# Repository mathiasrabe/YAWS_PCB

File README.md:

# PCB for IOT weather station

This is the PCB of my small IOT weather station. The weatherstation consists of the following parts:

- ATtiny85 and LT1763-3.3 for power control
- TP4056 to charge the li-ion battery with solar
- BME280 to measure temperature, humidity and pressure
- ESP8266 to connect to WiFi and send the reedings via MQTT

## pictures

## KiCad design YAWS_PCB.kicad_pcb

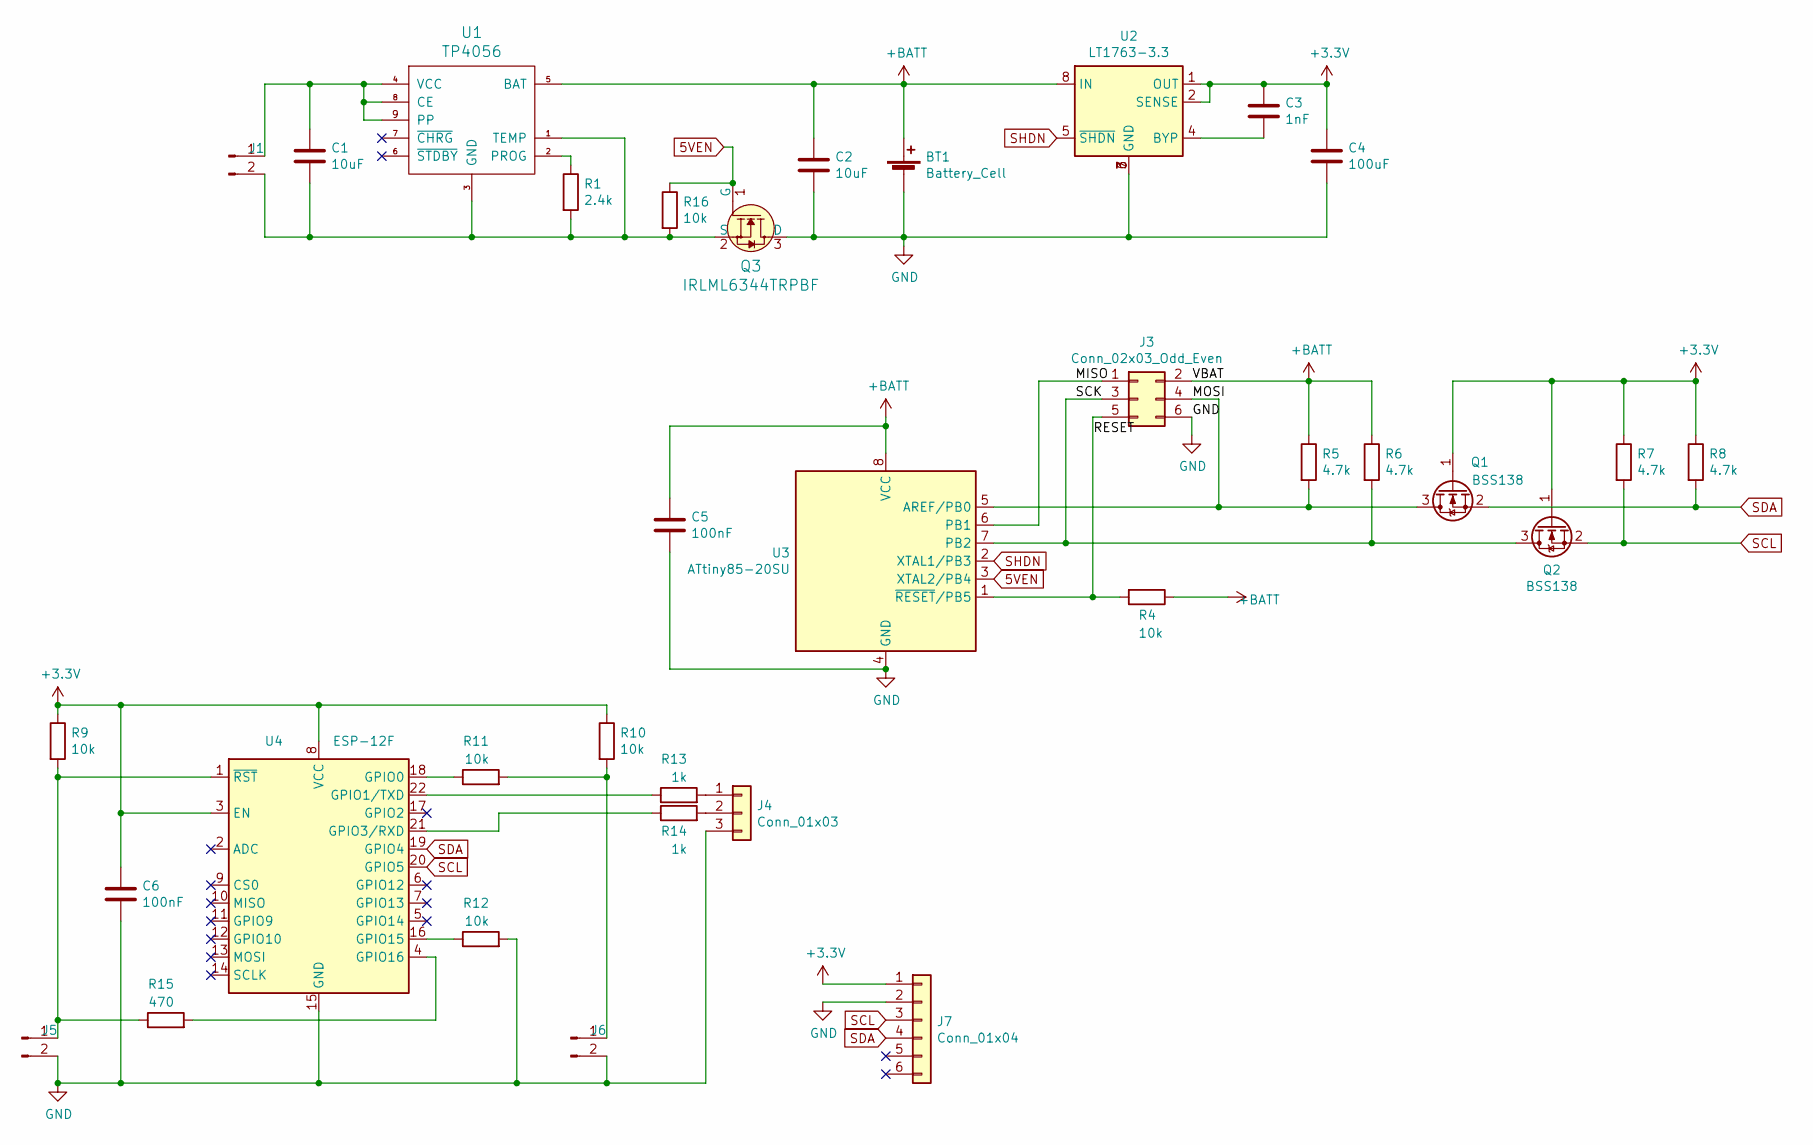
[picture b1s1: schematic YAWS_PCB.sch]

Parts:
BT1: Battery_Cell; BatteryHolder_Keystone_1042_1x18650
C1, C2: 10uF; C_0805_2012Metric
C3: 1nF; C_0805_2012Metric
C4: 100uF; CP_EIA-3528-21_Kemet-B_Pad1.50x2.35mm_HandSolder
C5, C6: 100nF; C_0805_2012Metric
J1, J5, J6: Conn_01x02_Male; PinHeader_2x01_P2.54mm_Vertical
J3: Conn_02x03_Odd_Even; PinHeader_2x03_P2.54mm_Vertical
J4: Conn_01x03; PinHeader_1x03_P2.54mm_Vertical
J7: Conn_01x04; PinSocket_1x06_P2.54mm_Vertical
Q1, Q2: BSS138; SOT-23
Q3: IRLML6344TRPBF; SOT-23-3; MPN IRLML6344TRPBF; Digi-Key_PN IRLML6344TRPBFCT-ND
R1: 2.4k; R_0805_2012Metric
R4, R9, R10, R11, R12, R16: 10k; R_0805_2012Metric
R5, R6, R7, R8: 4.7k; R_0805_2012Metric
R13, R14: 1k; R_0805_2012Metric
R15: 470; R_0805_2012Metric
U1: TP4056; TP4056_SOP-8-PP
U2: LT1763-3.3; SO-8_3.9x4.9mm_P1.27mm
U3: ATtiny85-20SU; SOIJ-8_5.3x5.3mm_P1.27mm
U4: ESP-12F; ESP-12E

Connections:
5VEN: Q3.1 (G), R16.1, U3.3 (XTAL2/PB4)
+3V3: C3.1, C4.1, C6.1, J7.1, Q1.1 (G), Q2.1 (G), R7.1, R8.1, R9.1, R10.1, U2.1 (OUT), U2.2 (SENSE), U4.3 (EN), U4.8 (VCC)
+BATT: BT1.1 (+), C2.1, C5.1, J3.2, R4.1, R5.1, R6.1, U1.5 (BAT), U2.8 (IN), U3.8 (VCC)
/MISO: J3.1, U3.6 (PB1)
/MOSI: J3.4, Q1.3 (D), R5.2, U3.5 (AREF/PB0)
/RESET: J3.5, R4.2, U3.1 (~RESET~/PB5)
/SCK: J3.3, Q2.3 (D), R6.2, U3.7 (PB2)
GND: BT1.2 (-), C2.2, C4.2, C5.2, C6.2, J3.6, J4.3, J5.2, J6.2, J7.2, Q3.3 (D), R12.2, U2.3 (GND), U2.6 (GND), U2.7 (GND), U3.4 (GND), U4.15 (GND)
unnamed: C1.1, J1.1, U1.4 (VCC), U1.8 (CE), U1.9 (PP)
unnamed: C1.2, J1.2, Q3.2 (S), R1.2, R16.2, U1.1 (TEMP), U1.3 (GND)
unnamed: C3.2, U2.4 (BYP)
unnamed: J4.1, R13.2
unnamed: J4.2, R14.2
unnamed: J5.1, R9.2, R15.1, U4.1 (~RST)
unnamed: J6.1, R10.2, R11.2
unnamed: R1.1, U1.2 (PROG)
unnamed: R11.1, U4.18 (GPIO0)
unnamed: R12.1, U4.16 (GPIO15)
unnamed: R13.1, U4.22 (GPIO1/TXD)
unnamed: R14.1, U4.21 (GPIO3/RXD)
unnamed: R15.2, U4.4 (GPIO16)
SCL: J7.3, Q2.2 (S), R7.2, U4.20 (GPIO5)
SDA: J7.4, Q1.2 (S), R8.2, U4.19 (GPIO4)
SHDN: U2.5 (~SHDN), U3.2 (XTAL1/PB3)

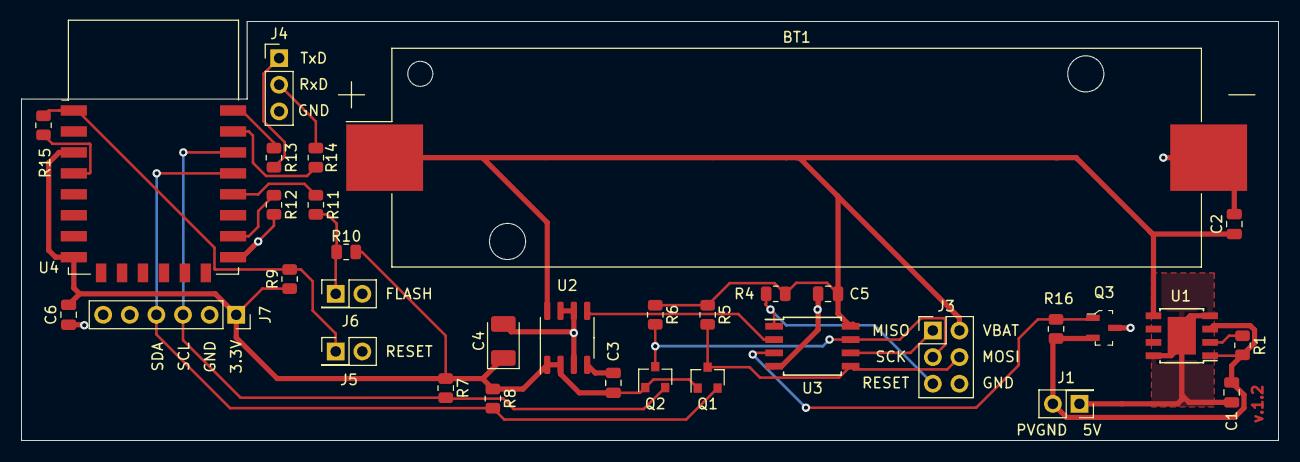
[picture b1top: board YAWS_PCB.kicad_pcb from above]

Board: 2 copper layers, 120.0 x 40.0 mm, 34 parts (0 on the bottom side), 24 nets.

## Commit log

2020-11-29 reworked README.md
2021-02-14 added MOSFET to disconnect TP4056 from battery
2021-03-13 reduced I2C pullups
